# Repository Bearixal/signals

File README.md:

# Signals

TODO:  
- Quarz auf Signalplatinen einfügen
- Buckconverter-Spannungsversorgungsplatine
- Optokopplerplatine

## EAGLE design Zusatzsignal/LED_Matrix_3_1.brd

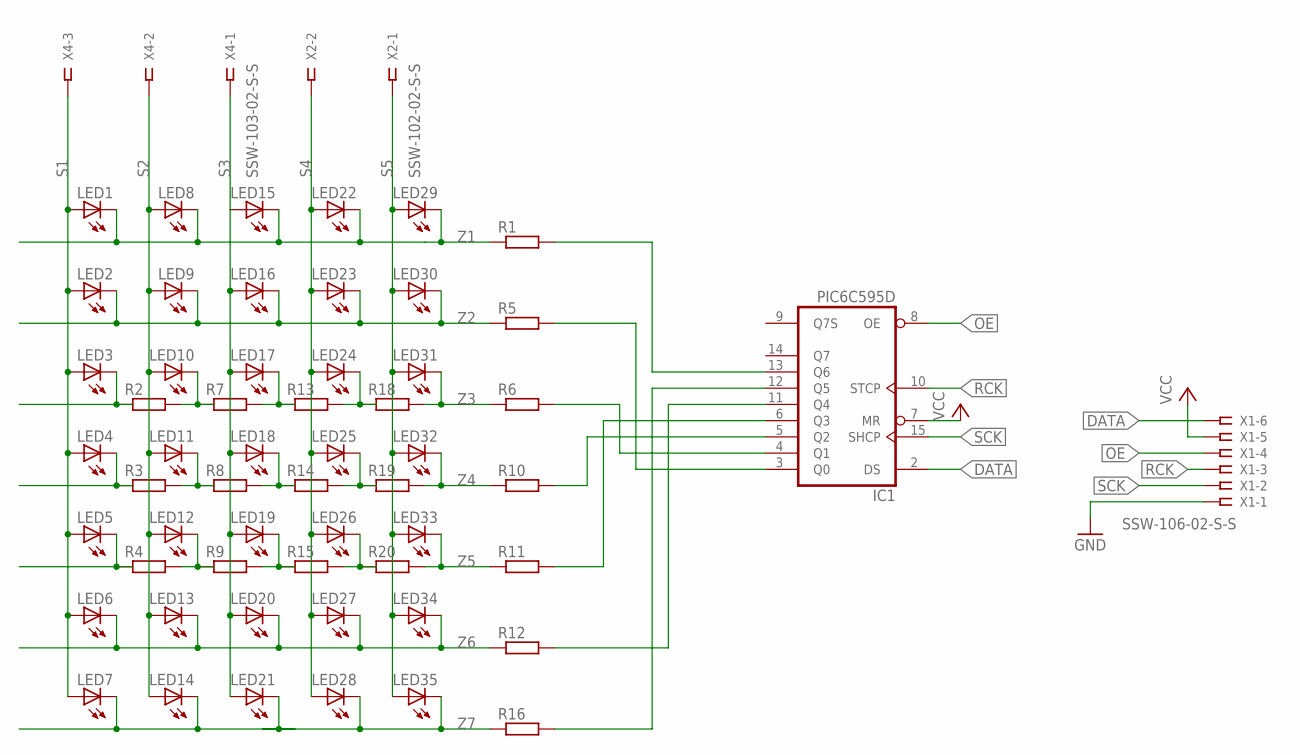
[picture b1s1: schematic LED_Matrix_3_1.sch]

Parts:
IC1: PIC6C595D; SO16
LED1, LED2, LED3, LED4, LED5, LED6, LED7, LED8, LED9, LED10, LED11, LED12, LED13, LED14, LED15, LED16, LED17, LED18, LED19, LED20, LED21, LED22, LED23, LED24, LED25, LED26, LED27, LED28, LED29, LED30, LED31, LED32, LED33, LED34, LED35: LEDCHIP-LED0603; CHIP-LED0603
R1, R2, R3, R4, R5, R6, R7, R8, R9, R10, R11, R12, R13, R14, R15, R16, R18, R19, R20: R-EU_R0603; R0603
X1: SSW-106-02-S-S
X2: SSW-102-02-S-S
X4: SSW-103-02-S-S

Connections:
DATA: IC1.2 (DS), X1.6
GND: IC1.16 (GND), X1.1
unnamed: IC1.13 (Q6), R1.2
unnamed: IC1.12 (Q5), R16.2
unnamed: IC1.11 (Q4), R12.2
unnamed: IC1.4 (Q1), R6.2
unnamed: IC1.3 (Q0), R5.2
unnamed: IC1.6 (Q3), R11.2
unnamed: IC1.5 (Q2), R10.2
unnamed: LED4.C, R3.1
unnamed: LED10.C, R2.2, R7.1
unnamed: LED17.C, R7.2, R13.1
unnamed: LED24.C, R13.2, R18.1
unnamed: LED25.C, R14.2, R19.1
unnamed: LED18.C, R8.2, R14.1
unnamed: LED11.C, R3.2, R8.1
unnamed: LED12.C, R4.2, R9.1
unnamed: LED19.C, R9.2, R15.1
unnamed: LED26.C, R15.2, R20.1
unnamed: LED5.C, R4.1
unnamed: LED3.C, R2.1
OE: IC1.8 (OE), X1.4
RCK: IC1.10 (STCP), X1.3
S1: LED1.A, LED2.A, LED3.A, LED4.A, LED5.A, LED6.A, LED7.A, X4.3
S2: LED8.A, LED9.A, LED10.A, LED11.A, LED12.A, LED13.A, LED14.A, X4.2
S3: LED15.A, LED16.A, LED17.A, LED18.A, LED19.A, LED20.A, LED21.A, X4.1
S4: LED22.A, LED23.A, LED24.A, LED25.A, LED26.A, LED27.A, LED28.A, X2.2
S5: LED29.A, LED30.A, LED31.A, LED32.A, LED33.A, LED34.A, LED35.A, X2.1
SCK: IC1.15 (SHCP), X1.2
VCC: IC1.1 (VCC), IC1.7 (MR), X1.5
Z1: LED1.C, LED8.C, LED15.C, LED22.C, LED29.C, R1.1
Z2: LED2.C, LED9.C, LED16.C, LED23.C, LED30.C, R5.1
Z3: LED31.C, R6.1, R18.2
Z4: LED32.C, R10.1, R19.2
Z5: LED33.C, R11.1, R20.2
Z6: LED6.C, LED13.C, LED20.C, LED27.C, LED34.C, R12.1
Z7: LED7.C, LED14.C, LED21.C, LED28.C, LED35.C, R16.1

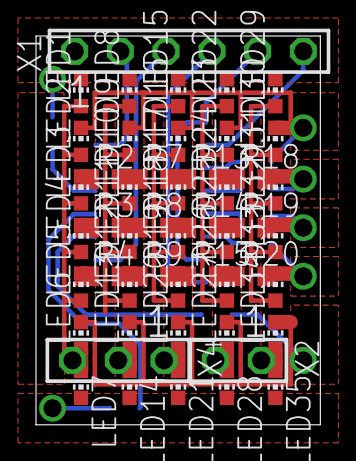
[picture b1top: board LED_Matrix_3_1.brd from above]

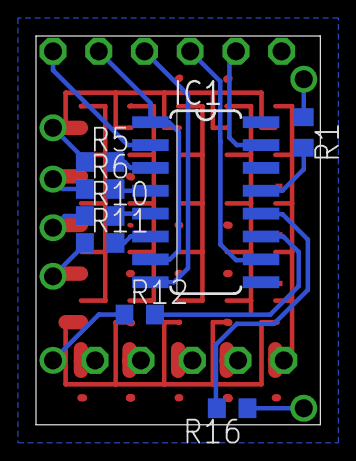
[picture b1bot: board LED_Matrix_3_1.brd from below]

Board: 2 copper layers, 15.8 x 21.6 mm, 58 parts (8 on the bottom side), 37 nets.

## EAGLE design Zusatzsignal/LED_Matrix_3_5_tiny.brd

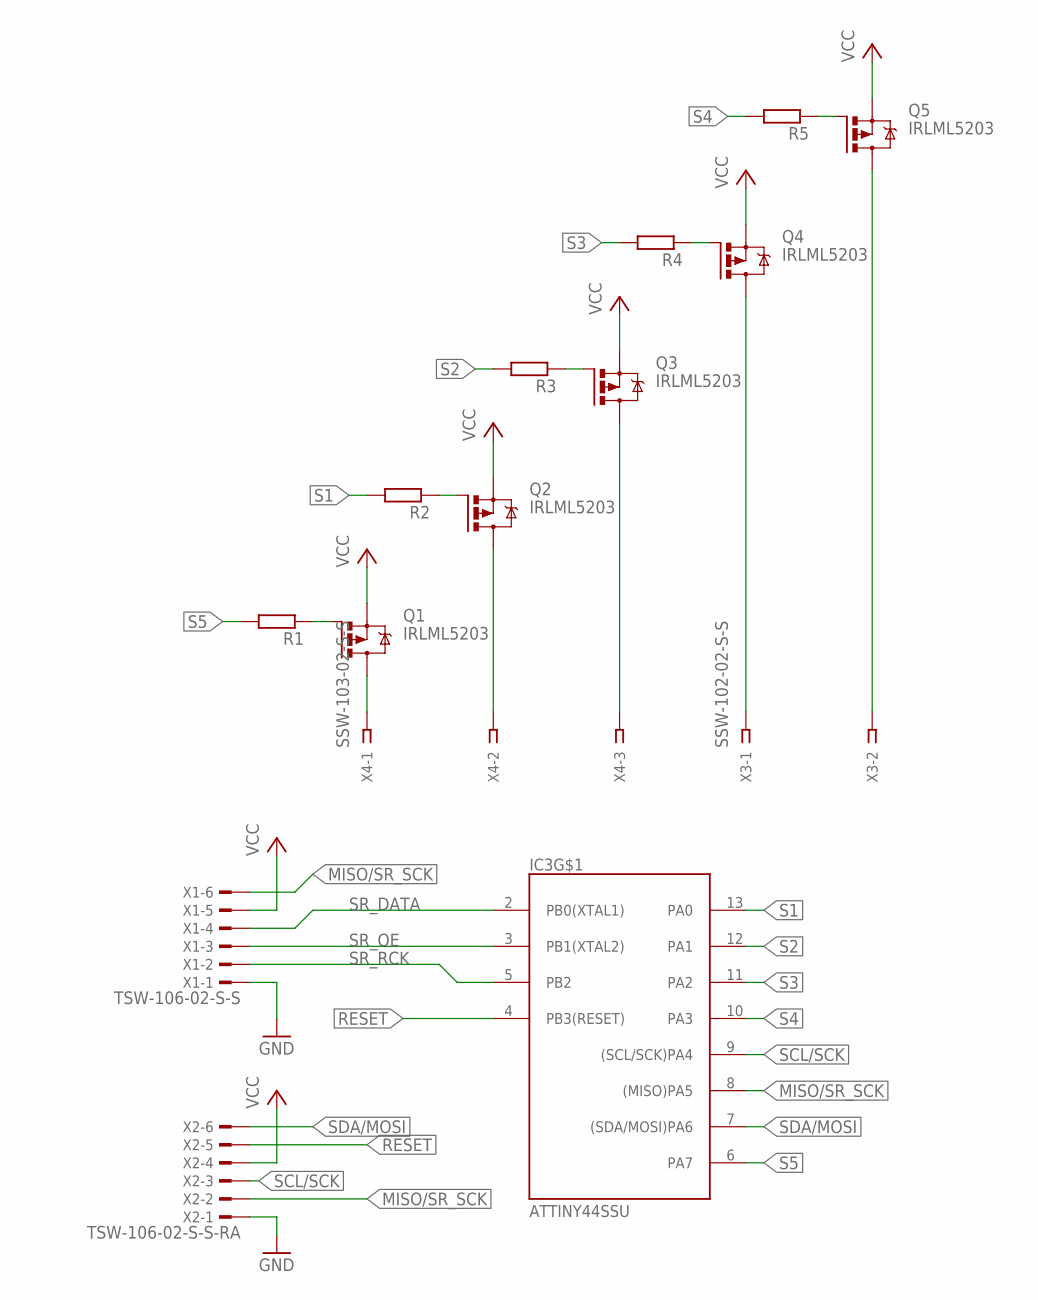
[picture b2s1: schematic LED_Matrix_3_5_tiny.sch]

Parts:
IC3: ATTINY44SSU; SO14
Q1, Q2, Q3, Q4, Q5: IRLML5203; MICRO3
R1, R2, R3, R4, R5: R-EU_R0603; R0603
X1: TSW-106-02-S-S
X2: TSW-106-02-S-S-RA
X3: SSW-102-02-S-S
X4: SSW-103-02-S-S

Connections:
GND: IC3.14 (GND), X1.1, X2.1
MISO/SR_SCK: IC3.8 ((MISO)PA5), X1.6, X2.2
unnamed: Q2.1 (G), R2.1
unnamed: Q3.1 (G), R3.1
unnamed: Q4.1 (G), R4.1
unnamed: Q5.1 (G), R5.1
unnamed: Q1.1 (G), R1.1
unnamed: Q5.3 (D), X3.2
unnamed: Q4.3 (D), X3.1
unnamed: Q3.3 (D), X4.3
unnamed: Q2.3 (D), X4.2
unnamed: Q1.3 (D), X4.1
RESET: IC3.4 (PB3(RESET)), X2.5
S1: IC3.13 (PA0), R2.2
S2: IC3.12 (PA1), R3.2
S3: IC3.11 (PA2), R4.2
S4: IC3.10 (PA3), R5.2
S5: IC3.6 (PA7), R1.2
SCL/SCK: IC3.9 ((SCL/SCK)PA4), X2.3
SDA/MOSI: IC3.7 ((SDA/MOSI)PA6), X2.6
SR_DATA: IC3.2 (PB0(XTAL1)), X1.4
SR_OE: IC3.3 (PB1(XTAL2)), X1.3
SR_RCK: IC3.5 (PB2), X1.2
VCC: IC3.1 (VCC), Q1.2 (S), Q2.2 (S), Q3.2 (S), Q4.2 (S), Q5.2 (S), X1.5, X2.4

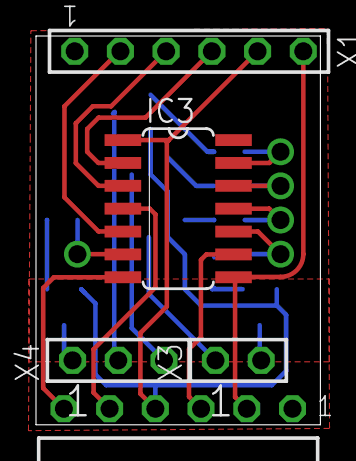
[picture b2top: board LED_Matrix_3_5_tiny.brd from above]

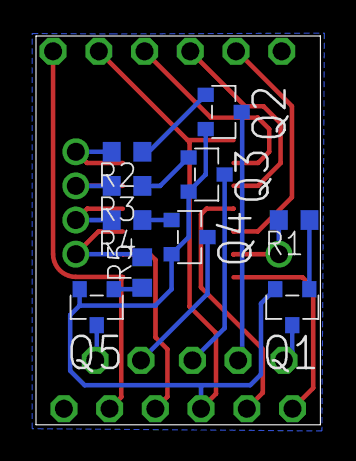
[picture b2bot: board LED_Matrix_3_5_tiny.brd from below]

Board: 2 copper layers, 15.8 x 21.6 mm, 15 parts (10 on the bottom side), 24 nets.

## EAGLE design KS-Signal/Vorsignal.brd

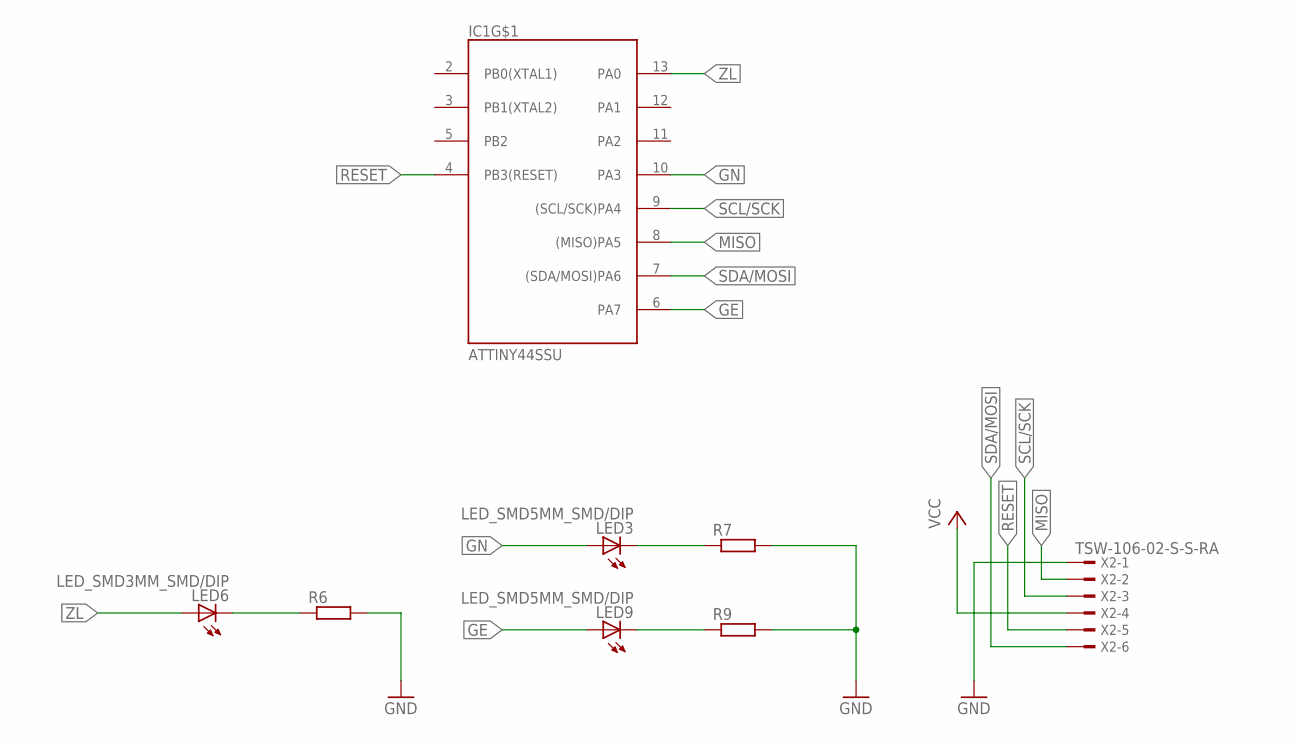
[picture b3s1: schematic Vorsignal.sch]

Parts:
IC1: ATTINY44SSU; SO14
LED3, LED9: LED_SMD5MM_SMD/DIP; 5MM_FLAT/DIP_SMDLED
LED6: LED_SMD3MM_SMD/DIP; 3MM_FLAT/DIP_SMDLED
R6, R7, R9: R-EU_R0603; R0603
X2: TSW-106-02-S-S-RA

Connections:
GE: IC1.6 (PA7), LED9.+ (A)
GN: IC1.10 (PA3), LED3.+ (A)
GND: IC1.14 (GND), R6.2, R7.2, R9.2, X2.1
MISO: IC1.8 ((MISO)PA5), X2.2
unnamed: LED9.- (C), R9.1
unnamed: LED6.- (C), R6.1
unnamed: LED3.- (C), R7.1
RESET: IC1.4 (PB3(RESET)), X2.5
SCL/SCK: IC1.9 ((SCL/SCK)PA4), X2.3
SDA/MOSI: IC1.7 ((SDA/MOSI)PA6), X2.6
VCC: IC1.1 (VCC), X2.4
ZL: IC1.13 (PA0), LED6.+ (A)

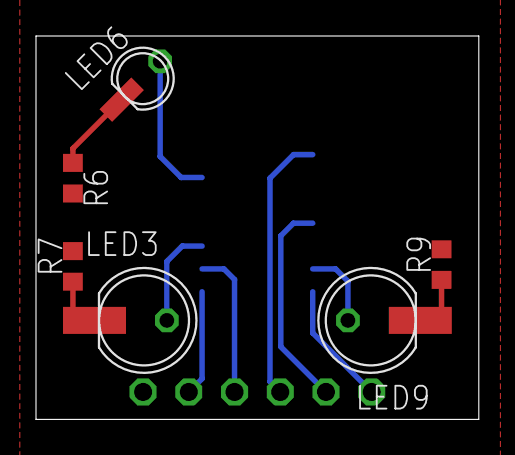
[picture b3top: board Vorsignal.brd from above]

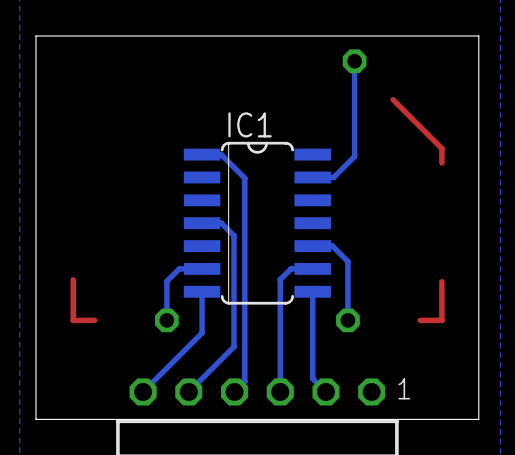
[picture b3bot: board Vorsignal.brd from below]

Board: 2 copper layers, 24.6 x 21.3 mm, 8 parts (2 on the bottom side), 12 nets.

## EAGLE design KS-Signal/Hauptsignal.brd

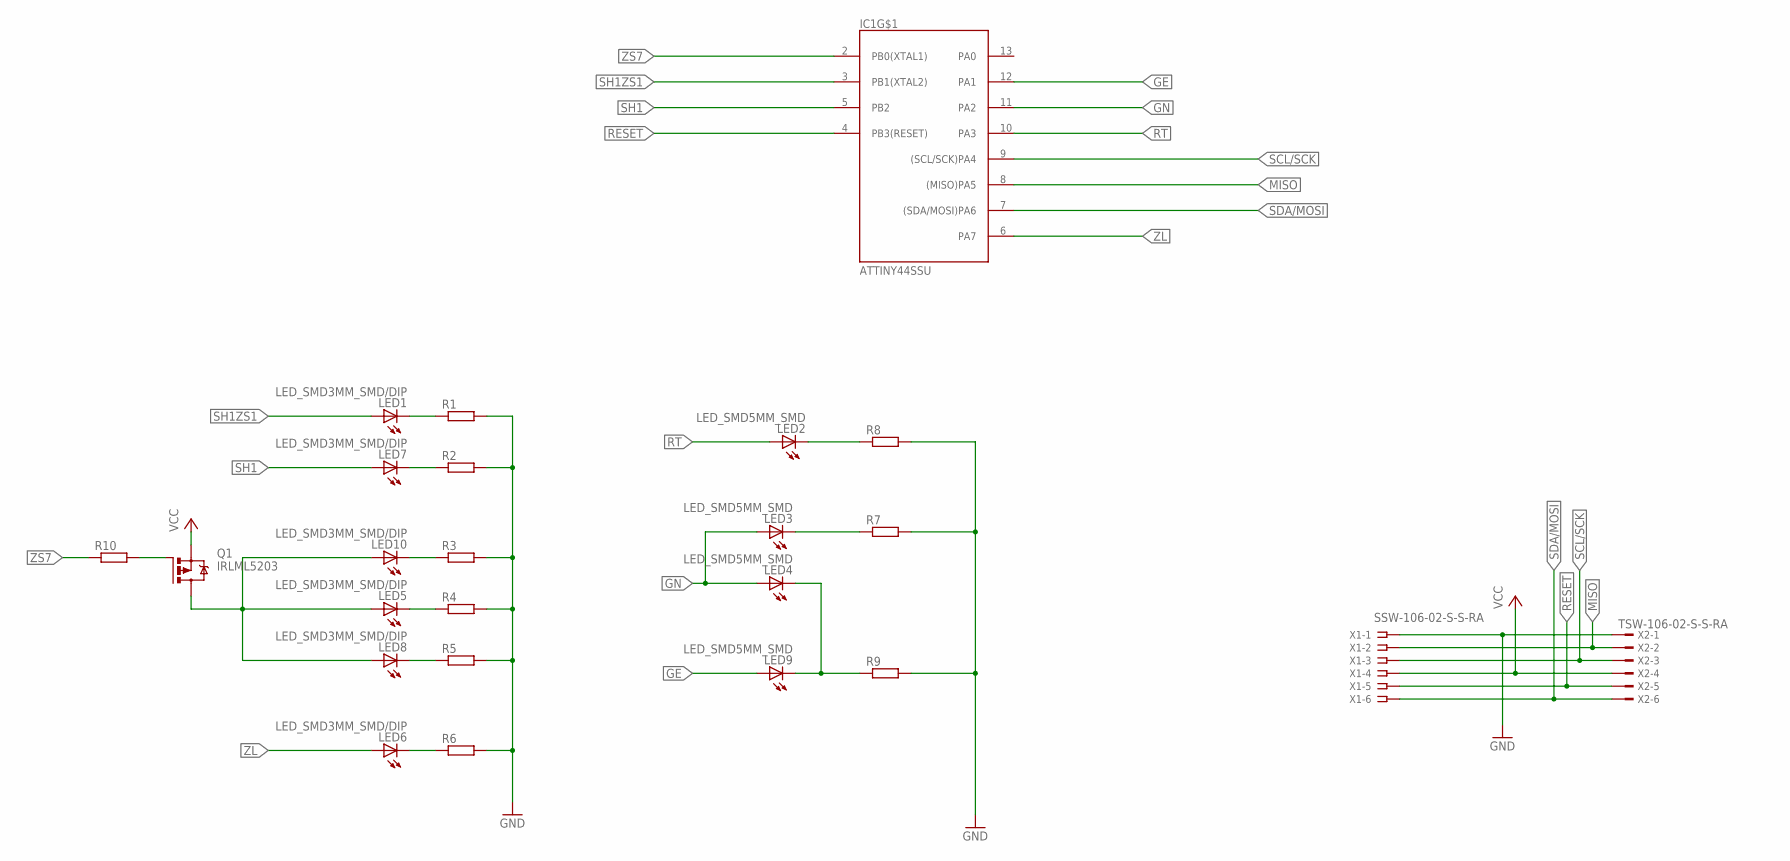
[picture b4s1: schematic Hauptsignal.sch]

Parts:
IC1: ATTINY44SSU; SO14
LED1, LED5, LED6, LED7, LED8, LED10: LED_SMD3MM_SMD/DIP; 3MM_FLAT/DIP_SMDLED
LED2, LED3, LED4, LED9: LED_SMD5MM_SMD; 5MM_FLAT_SMDLED
Q1: IRLML5203; MICRO3
R1, R2, R3, R4, R5, R6, R7, R8, R9, R10: R-EU_R0603; R0603
X1: SSW-106-02-S-S-RA
X2: TSW-106-02-S-S-RA

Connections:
GE: IC1.12 (PA1), LED9.+ (A)
GN: IC1.11 (PA2), LED3.+ (A), LED4.+ (A)
GND: IC1.14 (GND), R1.2, R2.2, R3.2, R4.2, R5.2, R6.2, R7.2, R8.2, R9.2, X1.1, X2.1
MISO: IC1.8 ((MISO)PA5), X1.2, X2.2
unnamed: LED4.- (C), LED9.- (C), R9.1
unnamed: LED6.- (C), R6.1
unnamed: LED8.- (C), R5.1
unnamed: LED5.- (C), R4.1
unnamed: LED10.- (C), R3.1
unnamed: LED7.- (C), R2.1
unnamed: LED1.- (C), R1.1
unnamed: LED3.- (C), R7.1
unnamed: LED2.- (C), R8.1
unnamed: LED5.+ (A), LED8.+ (A), LED10.+ (A), Q1.3 (D)
unnamed: Q1.1 (G), R10.2
RESET: IC1.4 (PB3(RESET)), X1.5, X2.5
RT: IC1.10 (PA3), LED2.+ (A)
SCL/SCK: IC1.9 ((SCL/SCK)PA4), X1.3, X2.3
SDA/MOSI: IC1.7 ((SDA/MOSI)PA6), X1.6, X2.6
SH1: IC1.5 (PB2), LED7.+ (A)
SH1ZS1: IC1.3 (PB1(XTAL2)), LED1.+ (A)
VCC: IC1.1 (VCC), Q1.2 (S), X1.4, X2.4
ZL: IC1.6 (PA7), LED6.+ (A)
ZS7: IC1.2 (PB0(XTAL1)), R10.1

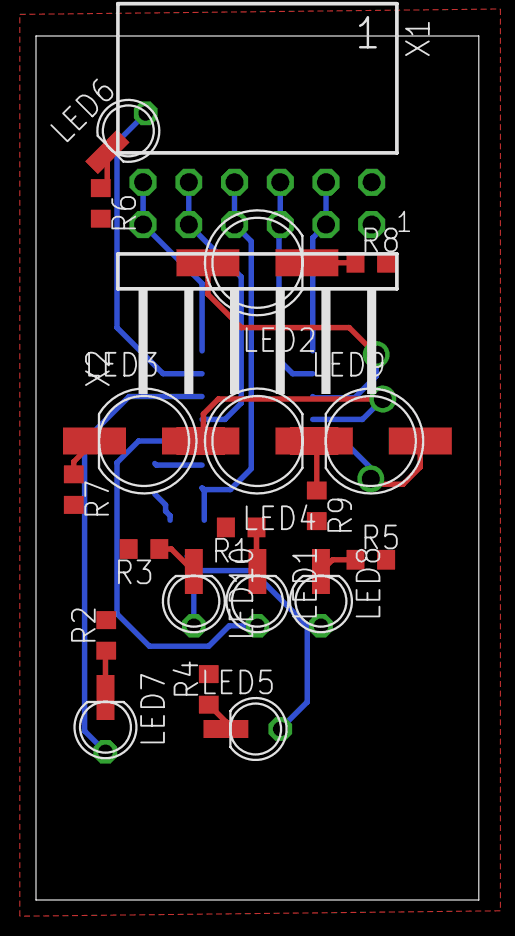
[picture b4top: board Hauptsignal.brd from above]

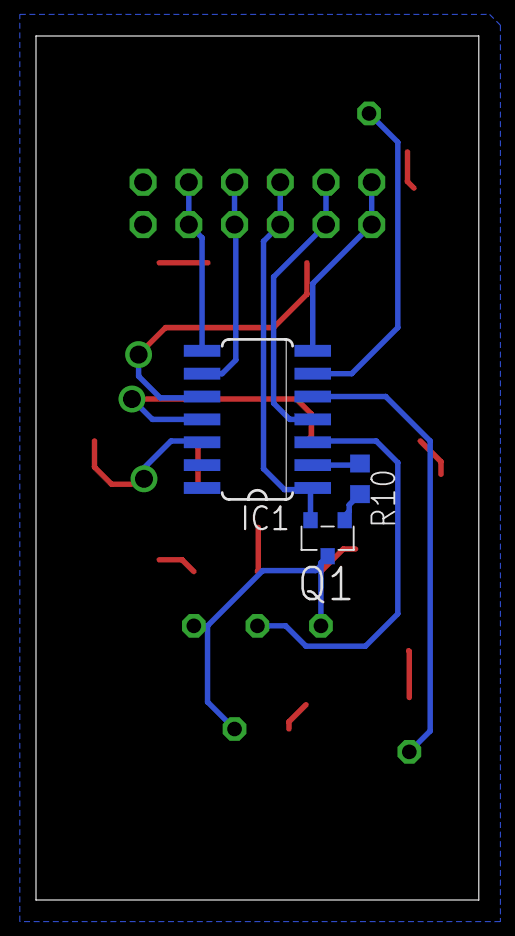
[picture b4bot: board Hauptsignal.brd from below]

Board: 2 copper layers, 24.6 x 48.0 mm, 24 parts (3 on the bottom side), 24 nets.

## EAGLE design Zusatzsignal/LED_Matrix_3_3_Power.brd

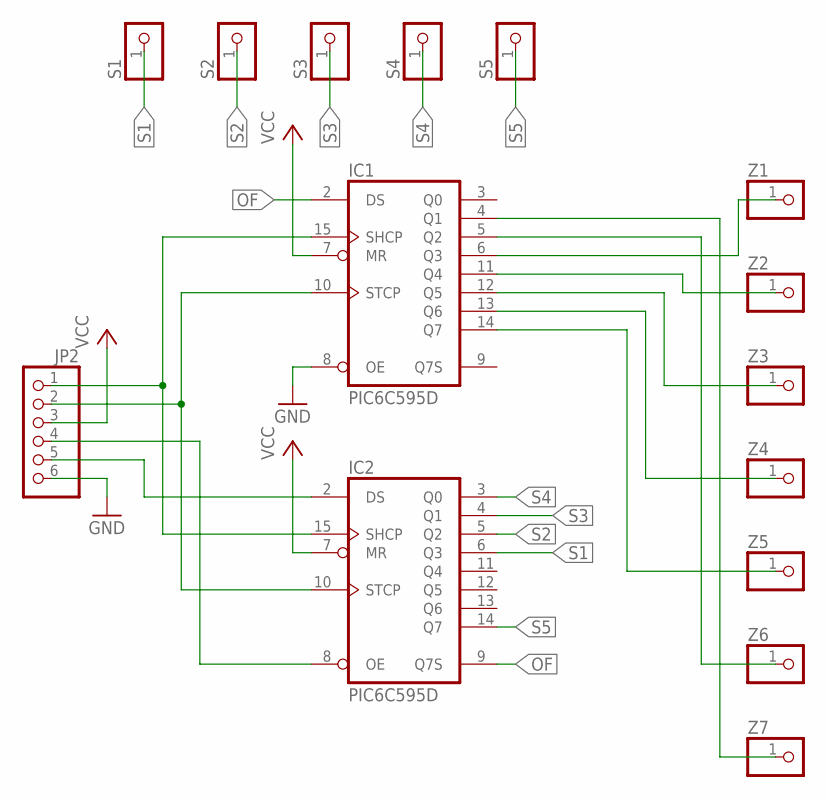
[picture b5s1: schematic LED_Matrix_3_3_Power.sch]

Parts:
IC1, IC2: PIC6C595D; SO16
JP2: PINHD-1X6; 1X06
S1, S2, S3, S4, S5: PINHD-1X1; 1X01
Z1, Z2, Z3, Z4, Z5, Z6, Z7: PINHD-1X1; 1X01

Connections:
GND: IC1.8 (OE), IC1.16 (GND), IC2.16 (GND), JP2.6
unnamed: IC1.10 (STCP), IC2.10 (STCP), JP2.2
unnamed: IC1.15 (SHCP), IC2.15 (SHCP), JP2.1
unnamed: IC2.2 (DS), JP2.5
unnamed: IC1.4 (Q1), Z7.1
unnamed: IC1.6 (Q3), Z1.1
unnamed: IC2.8 (OE), JP2.4
unnamed: IC1.5 (Q2), Z6.1
unnamed: IC1.14 (Q7), Z5.1
unnamed: IC1.13 (Q6), Z4.1
unnamed: IC1.12 (Q5), Z3.1
unnamed: IC1.11 (Q4), Z2.1
OF: IC1.2 (DS), IC2.9 (Q7S)
S1: IC2.6 (Q3), S1.1
S2: IC2.5 (Q2), S2.1
S3: IC2.4 (Q1), S3.1
S4: IC2.3 (Q0), S4.1
S5: IC2.14 (Q7), S5.1
VCC: IC1.1 (VCC), IC1.7 (MR), IC2.1 (VCC), IC2.7 (MR), JP2.3

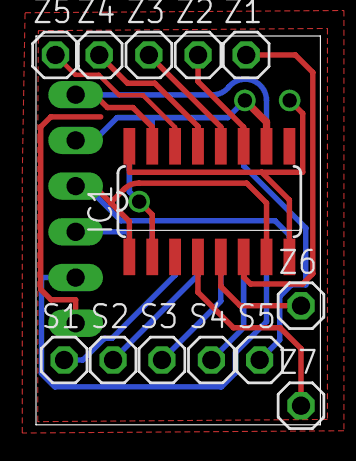
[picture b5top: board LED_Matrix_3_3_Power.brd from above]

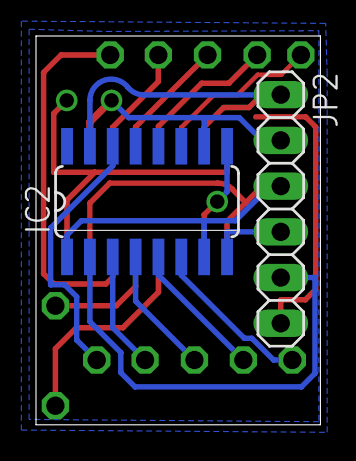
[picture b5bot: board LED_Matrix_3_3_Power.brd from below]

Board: 2 copper layers, 15.8 x 21.6 mm, 15 parts (2 on the bottom side), 19 nets.

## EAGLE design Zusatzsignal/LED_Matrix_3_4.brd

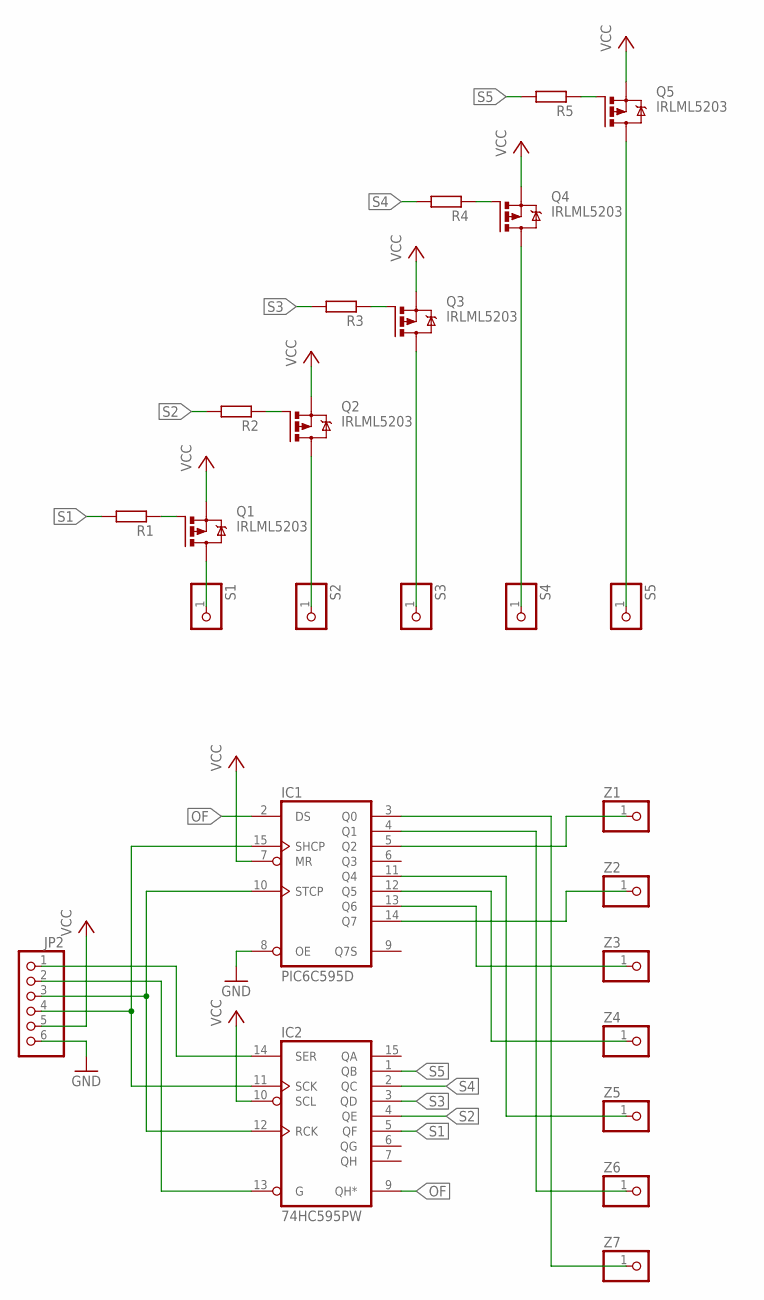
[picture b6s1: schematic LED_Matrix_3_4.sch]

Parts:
IC1: PIC6C595D; SO16
IC2: 74HC595PW; TSSOP16
JP2: PINHD-1X6; 1X06
Q1, Q2, Q3, Q4, Q5: IRLML5203; MICRO3
R1, R2, R3, R4, R5: R-EU_R0603; R0603
S1, S2, S3, S4, S5: PINHD-1X1; 1X01
Z1, Z2, Z3, Z4, Z5, Z6, Z7: PINHD-1X1; 1X01

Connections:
GND: IC1.8 (OE), IC1.16 (GND), IC2.8 (GND), JP2.6
unnamed: IC1.10 (STCP), IC2.12 (RCK), JP2.3
unnamed: IC1.15 (SHCP), IC2.11 (SCK), JP2.4
unnamed: IC2.14 (SER), JP2.1
unnamed: IC1.3 (Q0), Z7.1
unnamed: IC1.4 (Q1), Z6.1
unnamed: IC2.13 (G), JP2.2
unnamed: IC1.5 (Q2), Z1.1
unnamed: Q2.1 (G), R2.1
unnamed: IC1.14 (Q7), Z2.1
unnamed: IC1.13 (Q6), Z3.1
unnamed: IC1.12 (Q5), Z4.1
unnamed: IC1.11 (Q4), Z5.1
unnamed: Q3.1 (G), R3.1
unnamed: Q4.1 (G), R4.1
unnamed: Q5.1 (G), R5.1
unnamed: Q1.1 (G), R1.1
unnamed: Q5.3 (D), S5.1
unnamed: Q4.3 (D), S4.1
unnamed: Q3.3 (D), S3.1
unnamed: Q2.3 (D), S2.1
unnamed: Q1.3 (D), S1.1
OF: IC1.2 (DS), IC2.9 (QH*)
S1: IC2.5 (QF), R1.2
S2: IC2.4 (QE), R2.2
S3: IC2.3 (QD), R3.2
S4: IC2.2 (QC), R4.2
S5: IC2.1 (QB), R5.2
VCC: IC1.1 (VCC), IC1.7 (MR), IC2.10 (SCL), IC2.16 (VCC), JP2.5, Q1.2 (S), Q2.2 (S), Q3.2 (S), Q4.2 (S), Q5.2 (S)

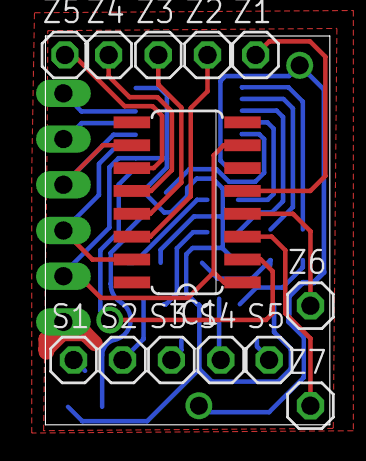
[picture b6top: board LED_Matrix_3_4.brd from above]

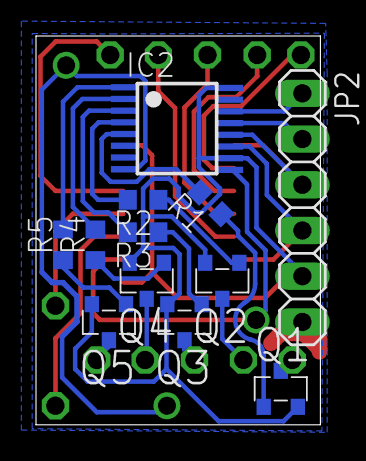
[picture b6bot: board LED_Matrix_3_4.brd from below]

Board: 2 copper layers, 15.8 x 21.6 mm, 25 parts (12 on the bottom side), 29 nets.

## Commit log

2017-10-02 Eaglefiles
2017-10-03 erste anpassungen
2017-10-03 Eaglebibs
2017-10-03 Layout LED Platine fertig
2017-10-03 Steuerungsplatine mit ATTiny44
2017-10-03 Verbesserung der Zusatzanzeigerplatine
    - Änderung des Layouts der Rückseite
    - Änderung der Durchführungen auf RM
    - Beseitigung von DRC-Fehlern
2017-10-03 Added SMDLEDpackages to EAGLE lib
2017-10-03 ZwischenS1
2017-10-03 Vordersteite fertig
2017-10-03 Rückseite fertig
2017-10-03 autosavefiles gelöscht
2017-10-04 Optimierung der Zusatzanzeiger & Hauptsignalplatine
    - Symmetrischere Auslegung
    - Entfernen von MISO/MISO connection zwischen Zusatzanzeiger und Hauptsignalschirm!
    -> Zusatzanzeiger-MISO auf Signalschirmplatine nicht mehr connected (NC)
    ->mögliches Auslesen des DCC-Signals über den MISO-Anschluss (MOSI und SCK für I2C)
2017-10-04 Vorsignale fertiggestellt
    - Vorsignalschirme fertiggestellt
    - Platinengrößen angepasst
    -> Achtung: Stecker und Pinbelegung unterschiedlich zwischen den beiden Vorsignaltypen
2017-10-04 deleted autosavefiles
2017-10-04 TODO
2017-10-09 Neuorganisation des Zusatzanzeigers
    -> Werte begradigt und alle LEDs korrigiert
